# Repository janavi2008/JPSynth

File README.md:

# JPSynth
a finger drum machine with 8 drum pads, gesture controls, and its own amp and speaker. its also got a rotary encoder and an oled screen. the pads are piezo discs, and theres a distance sensor, so moving your hand up and down can bend the pitch or distort the sound

# Design
Ive used waveshare esp32 s3 zero module as the microcontroller, 8 piezoelectric discs, a vl53l0x sensor, an EC11 rotary encoder, an 1.3in oled screen, 2 pushbuttons, a MAX98357A amp module, and a 3W 8ohm speaker. i designed the enclosure, lid and caps for the drum pads in CAD.
each pad acts as its own drum - a kick drum, hi-hat, snare, crash, ride, mid tom, high tom and floor tom. one of the buttons will act as a hi-hat pedal. the rotary encoder can control the volume or change the kit. the distance sensor measures how high your left hand is and bends the pitch according to where you move it. the oled screen dispays the settings selected, and shows sound waves while playing.

the firmware is barebones, only the actual drum part and the gesture controls is done. the oled and a couple buttens are left, which ill do during the build as i didnt get enough time.

Schematic:

Pcb:

CAD:

# BOM

| Part | Quantity | Price | Vendor |
| :--- | :---: | :---: | :--- |
| Waveshare ESP32 S3 Zero | 1 | $6.31 | Robu.in |
| VL53L0X sensor | 1 | - | Robu.in |
| MAX98357 module | 1 | - | Robu.in |
| 1.3in OLED display | 1 | - | Robu.in |
| 3W 8Ohm speaker | 1 | - | Robu.in |
| 27mm piezo disc | 8 | $3 | Robu.in |
| smd BAT54S | 8 | $0.2 | Robu.in |
| 0805 smd 1M ohm resistor | 8 | $0.2 | Robu.in |
| 0805 smd 10k ohm resistor | 8 | $0.2 | Robu.in |
| EVA foam 5mm | - | $2 | Amazon.in |
| EC11 rotary encoder | 1 | $0.5 | Robu.in |
| SMD push buttons | 2 | $0.3 | Robu.in |
| 0805 smd 10uf capacitor | 1 | $0.1 | Robu.in |
| 0805 smd 0.1uf capacitor | 3 | $0.1 | Robu.in |
| PCB | 1 | $10 | zbotic.in |
| 3d prints | - | - | - |

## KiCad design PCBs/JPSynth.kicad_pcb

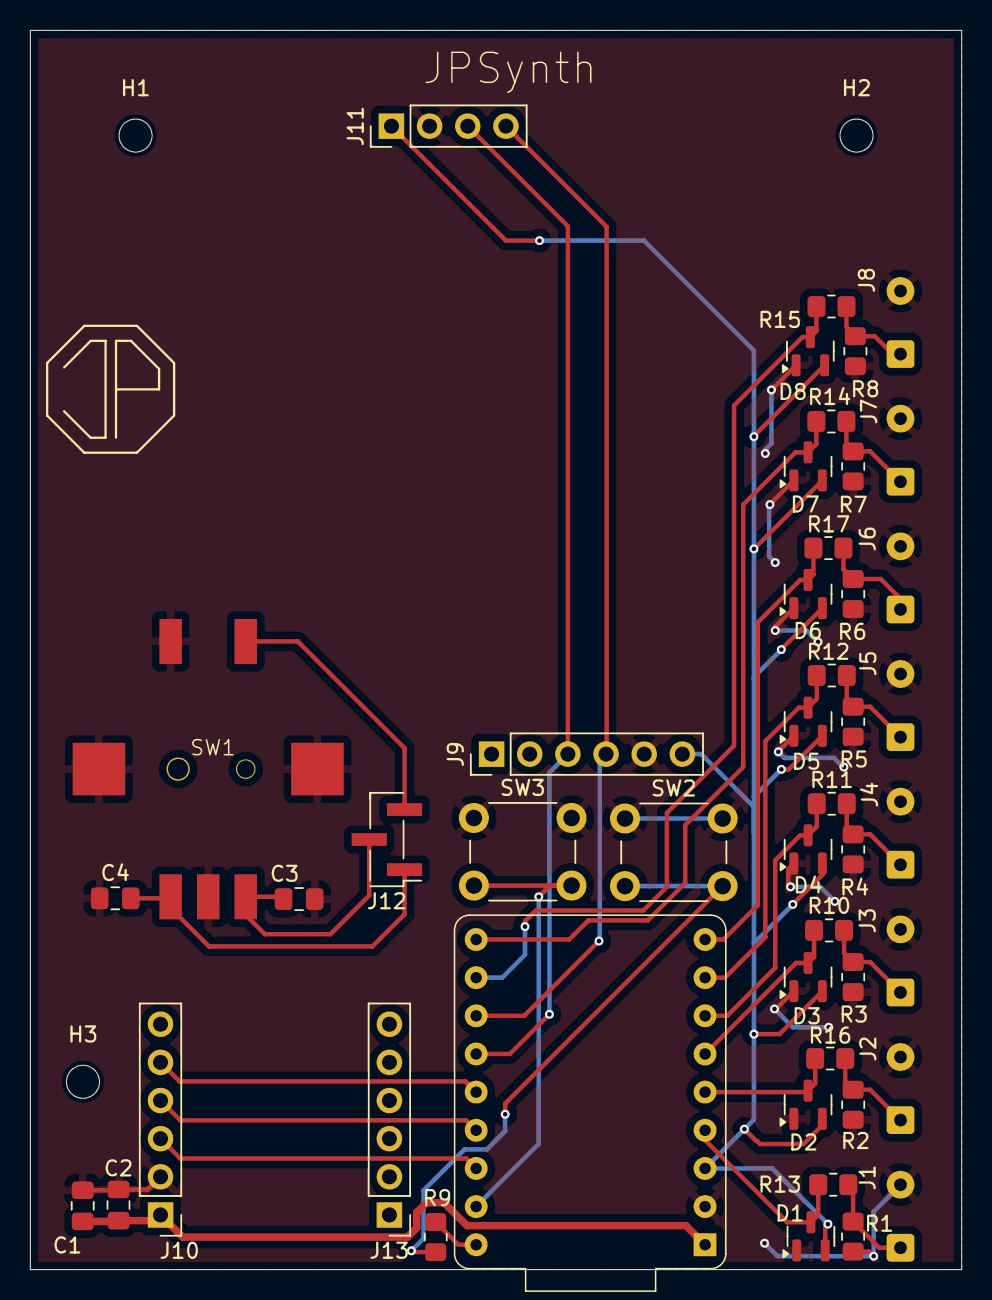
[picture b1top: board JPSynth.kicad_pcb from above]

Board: 2 copper layers, 62.0 x 82.5 mm, 49 parts (0 on the bottom side), 30 nets.

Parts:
C1: 10uF; C_0805_2012Metric_Pad1.18x1.45mm_HandSolder
C2: 0.1uF; C_0805_2012Metric_Pad1.18x1.45mm_HandSolder
C3, C4: 0.1uf; C_0805_2012Metric_Pad1.18x1.45mm_HandSolder
D1, D2, D3, D4, D5, D6, D7, D8: BAT54S; SOT-23
H1, H2, H3: MountingHole; MountingHole_2.2mm_M2
J1: Piezo1; SolderWire-0.25sqmm_1x02_P4.2mm_D0.65mm_OD1.7mm
J2: Piezo2; SolderWire-0.25sqmm_1x02_P4.2mm_D0.65mm_OD1.7mm
J3: Piezo3; SolderWire-0.25sqmm_1x02_P4.2mm_D0.65mm_OD1.7mm
J4: Piezo4; SolderWire-0.25sqmm_1x02_P4.2mm_D0.65mm_OD1.7mm
J5: Piezo5; SolderWire-0.25sqmm_1x02_P4.2mm_D0.65mm_OD1.7mm
J6: Piezo6; SolderWire-0.25sqmm_1x02_P4.2mm_D0.65mm_OD1.7mm
J7: PIezo7; SolderWire-0.25sqmm_1x02_P4.2mm_D0.65mm_OD1.7mm
J8: Piezo8; SolderWire-0.25sqmm_1x02_P4.2mm_D0.65mm_OD1.7mm
J9: VL53L0X; PinHeader_1x06_P2.54mm_Vertical
J10: MAX98357A -1; PinHeader_1x06_P2.54mm_Vertical
J11: OLED; PinHeader_1x04_P2.54mm_Vertical
J12: ESP32-extra pads; PinHeader_1x03_P2.00mm_Vertical_SMD_Pin1Left
J13: MAX98357A -2; PinHeader_1x06_P2.54mm_Vertical
R1, R2, R3, R4, R5, R6, R7, R8: 1M; R_0805_2012Metric_Pad1.20x1.40mm_HandSolder
R9: 1k; R_0805_2012Metric_Pad1.20x1.40mm_HandSolder
R10, R11, R12, R13, R14, R15, R16, R17: 10k; R_0805_2012Metric_Pad1.20x1.40mm_HandSolder
SW1: RotaryEncoder_Switch_MP; rotary encoder
SW2, SW3: SW_Push; SW_PUSH_6mm
U1: ESP32-S3-Zero; Waveshare-ESP32-S3-Zero

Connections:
/+3V3: D1.2 (K), D2.2 (K), D3.2 (K), D4.2 (K), D5.2 (K), D6.2 (K), D7.2 (K), D8.2 (K), J9.6, J11.1, U1.3 (3V3(OUT))
/+5V: C1.1, C2.1, J10.1, U1.1 (VDD)
/GND: C1.2, C2.2, C3.2, C4.1, D1.1 (A), D2.1 (A), D3.1 (A), D4.1 (A), D5.1 (A), D6.1 (A), D7.1 (A), D8.1 (A), J1.2, J2.2, J3.2, J4.2, J5.2, J6.2, J7.2, J8.2, J9.5, J10.2, J11.2, R1.2, R2.2, R3.2, R4.2, R5.2, R6.2, R7.2, R8.2, SW1.1, SW1.3, SW1.5, SW2.1, SW3.1, U1.2 (GND)
/GPIO1_D1: D1.3 (COM), R13.2, U1.4 (GPIO1)
/GPIO2_D2: D2.3 (COM), R16.2, U1.5 (GPIO2)
/GPIO3_D3: D3.3 (COM), R10.2, U1.6 (GPIO3)
/GPIO4_D4: D4.3 (COM), R11.2, U1.7 (GPIO4)
/GPIO5_D5: D5.3 (COM), R12.2, U1.8 (GPIO5)
/GPIO6_D6: D6.3 (COM), R17.2, U1.9 (GPIO6)
/GPIO7_D7: D7.3 (COM), R14.2, U1.10 (GPIO7)
/GPIO8_D8: D8.3 (COM), R15.2, U1.11 (GPIO8)
/GPIO9_SDA: J9.4, J11.4, U1.12 (GPIO9)
/GPIO10_SCL: J9.3, J11.3, U1.13 (GPIO10)
/GPIO11_DIN: J10.5, U1.14 (GPIO11)
/GPIO12_BCLK: J10.4, U1.15 (GPIO12)
/GPIO13_LRC: J10.3, U1.16 (GPIO13)
/GPIO14: J12.3, SW1.6
/GPIO15: C3.1, J12.2, SW1.4
/GPIO16: C4.2, J12.1, SW1.2
/SW2_TX: R9.2, U1.18 (TX)
/SW3_RX: SW3.2, U1.17 (RX)
unnamed: J1.1, R1.1, R13.1
unnamed: J2.1, R2.1, R16.1
unnamed: J3.1, R3.1, R10.1
unnamed: J4.1, R4.1, R11.1
unnamed: J5.1, R5.1, R12.1
unnamed: J6.1, R6.1, R17.1
unnamed: J7.1, R7.1, R14.1
unnamed: J8.1, R8.1, R15.1
unnamed: R9.1, SW2.2
